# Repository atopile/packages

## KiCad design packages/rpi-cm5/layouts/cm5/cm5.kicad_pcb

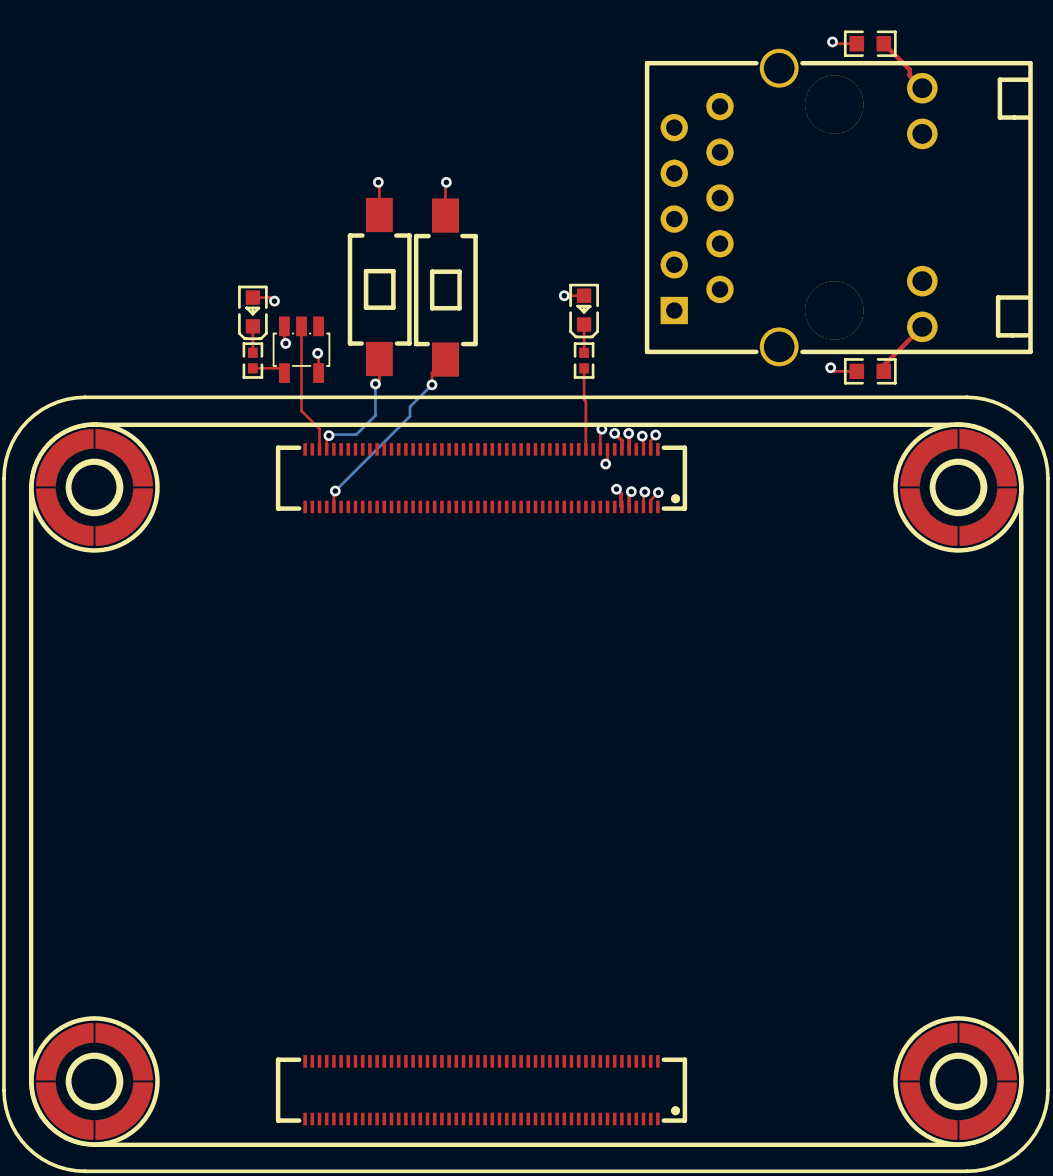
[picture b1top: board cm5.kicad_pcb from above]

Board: 4 copper layers, 17 parts (0 on the bottom side), 23 nets.

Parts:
CN1, CN2: CONN-SMD_DF40C-100DS-0.4V-51
D1: LED0603-RD-YELLOW
D2: LED0603-RD
R1, R2: 2kΩ ±1% 62.5mW; R0402
R3, R4: 470Ω ±1% 100mW; R0603
RJ1: RJ45-TH_HR911130A
SW1, SW2: SW-SMD_L6.0-W3.3-LS8.0
U1: SOT-23-5_L3.0-W1.7-P0.95-LS2.8-BR
U2, U3, U4, U5: SMD_BD5.6-D4.1
U6: cm5

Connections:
-pins[2]-0: CN1.99, RJ1.P8
-pins[3]: CN1.2, RJ1.P4
-pins[4]-0: CN1.98, RJ1.P9
-pins[5]: CN1.3, RJ1.P7
-pins[8]: CN1.96, RJ1.P6
-pins[9]: CN1.5, RJ1.P3
-pins[10]: CN1.95, RJ1.P5
-pins[11]: CN1.6, RJ1.P2
-pins[14]: CN1.93, RJ1.12
-pins[16]: CN1.92, RJ1.13
-pins[76]: CN1.57, CN1.58, CN1.59, CN1.60, CN1.61, CN1.62
-pins[92]: CN1.54, SW1.1
Y: R2.2, U1.4
cm5-cathode-0: D1.1, R1.1
cm5-cathode-1: D2.1, R2.1
cm5-pins[20]: CN1.90, R1.2
cm5-pins[87]-0: CN1.44, CN1.45
cm5-pins[94]: CN1.53, U1.2
gnd: CN1.1, CN1.4, CN1.7, CN1.11, CN1.16, CN1.21, CN1.26, CN1.30, CN1.33, CN1.37, CN1.49, CN1.65, CN1.68, CN1.71, CN1.74, CN1.79, CN1.84, CN1.89, CN1.94, CN1.97, CN1.100, CN2.4, CN2.7, CN2.10, CN2.13, CN2.16, CN2.19, CN2.22, CN2.28, CN2.31, CN2.34, CN2.37, CN2.40, CN2.43, CN2.46, CN2.49, CN2.52, CN2.55, CN2.58, CN2.61, CN2.64, CN2.67, CN2.70, CN2.73, CN2.82, CN2.85, CN2.88, CN2.91, CN2.94, CN2.97, RJ1.SHIELD0, RJ1.SHIELD1, SW1.2, SW2.2, U1.3, U2.1, U2.2, U2.3, U2.4, U3.1, U3.2, U3.3, U3.4, U4.1, U4.2, U4.3, U4.4, U5.1, U5.2, U5.3, U5.4
hv: CN1.39, CN1.42, CN1.43, D1.2, D2.2, R3.1, R4.1, U1.5
pins[91]: CN1.46, SW2.1
rj45-anode-0: R3.2, RJ1.11
rj45-anode-1: R4.2, RJ1.14

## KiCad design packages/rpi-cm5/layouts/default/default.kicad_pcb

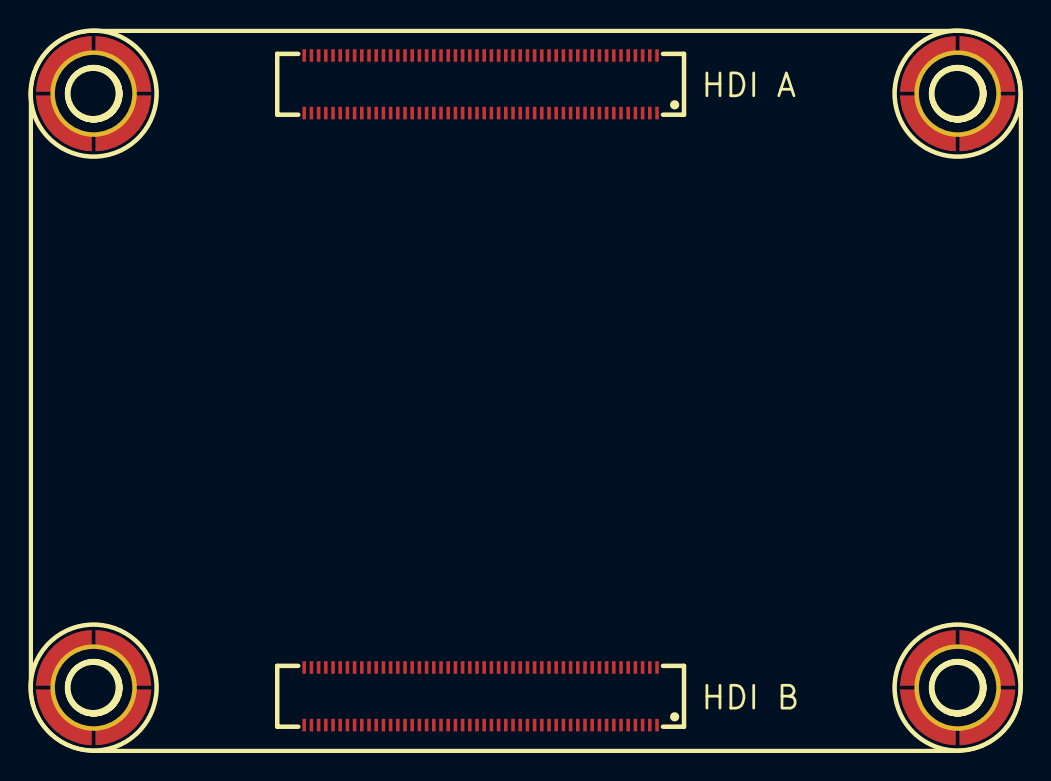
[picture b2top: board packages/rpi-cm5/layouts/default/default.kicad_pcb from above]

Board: 4 copper layers, 7 parts (0 on the bottom side), 5 nets, no tracks yet.

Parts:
CN1, CN2: CONN-SMD_DF40C-100DS-0.4V-51
U1, U2, U3, U4: SMD_BD5.6-D4.1
U5: cm5

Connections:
lv: CN1.1, CN1.4, CN1.7, CN1.11, CN1.16, CN1.21, CN1.26, CN1.30, CN1.33, CN1.37, CN1.49, CN1.65, CN1.68, CN1.71, CN1.74, CN1.79, CN1.84, CN1.89, CN1.94, CN1.97, CN1.100, CN2.4, CN2.7, CN2.10, CN2.13, CN2.16, CN2.22, CN2.28, CN2.31, CN2.34, CN2.37, CN2.40, CN2.43, CN2.46, CN2.49, CN2.52, CN2.55, CN2.58, CN2.61, CN2.64, CN2.67, CN2.70, CN2.73, CN2.82, CN2.85, CN2.88, CN2.91, CN2.94, CN2.97
power_1v8-hv: CN1.44, CN1.45
power_3v3-hv: CN1.42, CN1.43
power_3v3-lv: U1.1, U1.2, U1.3, U1.4, U1.5, U2.1, U2.2, U2.3, U2.4, U2.5, U3.1, U3.2, U3.3, U3.4, U3.5, U4.1, U4.2, U4.3, U4.4, U4.5
power_5v-hv: CN1.57, CN1.58, CN1.59, CN1.60, CN1.61, CN1.62

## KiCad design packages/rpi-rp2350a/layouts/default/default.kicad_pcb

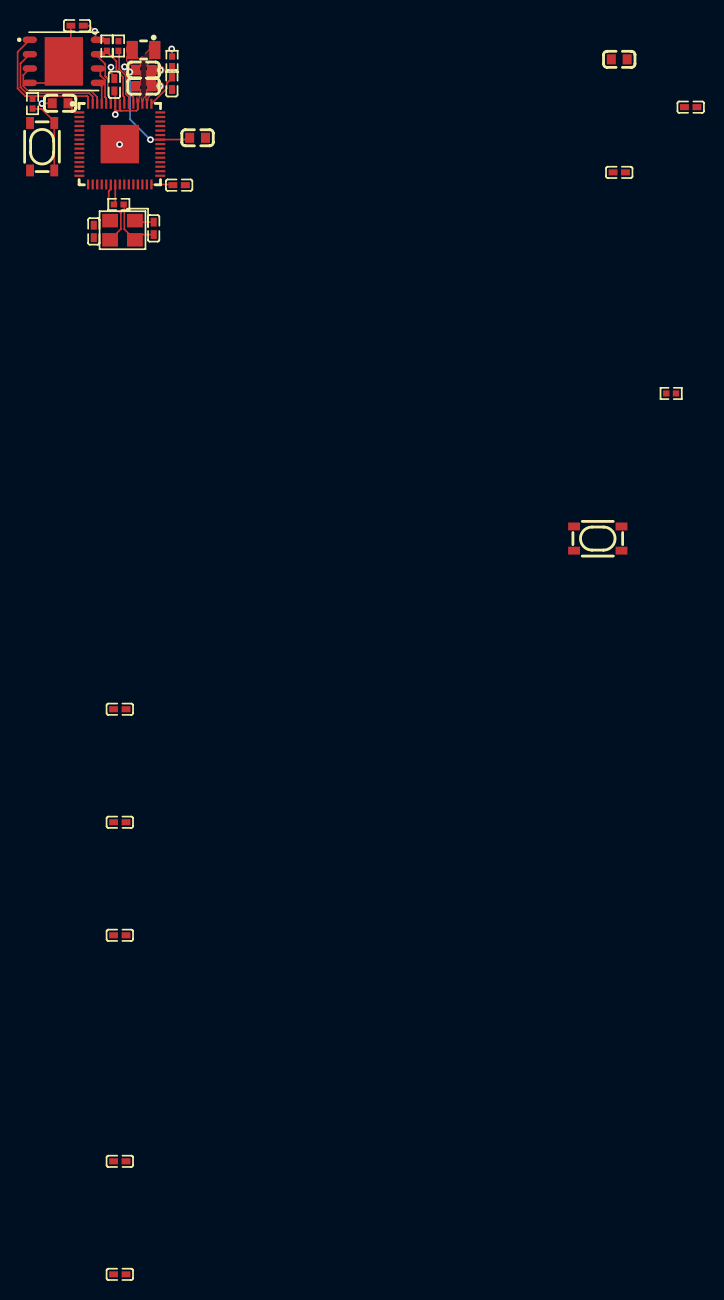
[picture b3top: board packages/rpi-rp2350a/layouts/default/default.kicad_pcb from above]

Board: 2 copper layers, 30 parts (0 on the bottom side), 20 nets.

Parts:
C1, C2, C5, C6, C7, C8, C9, C10, C11, C15, C16, C17, C18: 100nF ±10% 16V X7R; C0402-b3ef17
C3, C4, C12, C13, C14: 4.7µF ±10% 10V X5R; C0603-bd72f6
L1: IND-SMD_L2.0-W1.6_AOTA-B201610S3R3-101-T-1c9b19
R1, R2: 27Ω ±1% 62.5mW; R0402-56259e
R3, R6: 10kΩ ±1% 62.5mW; R0402-56259e
R4: 1kΩ ±1% 62.5mW; R0402-56259e
R5: 33Ω ±1% 62.5mW; R0402-56259e
U1: QFN-60_L7.0-W7.0-P0.40-TL-EP3.4-c01870
U2: WSON-8_L6.0-W5.0-P1.27-BL-EP-5c84f1
U3, U4: KEY-SMD_4P-L4.2-W3.2-P2.20-LS4.6-a2ccf0
XTAL1: CRYSTAL-SMD_4P-L3.2-W2.5-BL-e199c8

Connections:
QSPI_SCLK: U1.56, U2.6
QSPI_SD0: U1.57, U2.5
QSPI_SD1: U1.59, U2.2
QSPI_SD2: U1.58, U2.3
QSPI_SD3: U1.55, U2.7
QSPI_SS: R3.1, U1.60, U2.1
RUN: R6.1, U1.26
USB_DM: R1.2, U1.51
USB_DP: R2.2, U1.52
VREG_AVDD: C18.1, R5.2, U1.46
VREG_FB: C1.1, C2.1, C3.1, C4.1, L1.1, U1.6, U1.23, U1.39, U1.50
VREG_LX: L1.2, U1.48
XIN: C17.1, U1.21, XTAL1.3
XOUT: R4.2, U1.22
crystal_oscillator-net: C16.1, R4.1, XTAL1.4
gnd: U3.3, U3.4
gnd-1: C1.2, C2.2, C3.2, C4.2, C5.2, C6.2, C7.2, C8.2, C9.2, C10.2, C11.2, C12.2, C13.2, C14.2, C15.2, C16.2, C17.2, C18.2, U1.47, U1.61, U2.4, U2.9, U4.3, U4.4, XTAL1.1
hv: C5.1, C6.1, C7.1, C8.1, C9.1, C10.1, C11.1, C12.1, C13.1, C14.1, C15.1, R5.1, U1.1, U1.11, U1.20, U1.30, U1.38, U1.45, U1.49, U1.53, U1.54, U2.8
net: R6.2, U4.1, U4.2
net-1: R3.2, U3.1, U3.2

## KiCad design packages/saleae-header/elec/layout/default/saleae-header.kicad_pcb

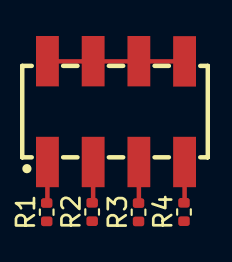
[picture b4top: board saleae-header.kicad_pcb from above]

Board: 2 copper layers, 5 parts (0 on the bottom side), 5 nets.

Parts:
R1, R2, R3, R4: Chip Resistor - Surface Mount 1KOhms ±5% 1/16W 04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; R0402
U1: HDR-SMD_8P-P2.54-V-M-R2-C4-LS7.4

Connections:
_1: R1.2, U1.1
_3: R2.2, U1.3
_5: R3.2, U1.5
_7: R4.2, U1.7
gnd: U1.2, U1.4, U1.6, U1.8

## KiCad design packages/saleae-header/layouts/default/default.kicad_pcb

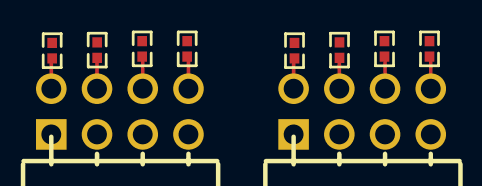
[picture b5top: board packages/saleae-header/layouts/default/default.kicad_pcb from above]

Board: 2 copper layers, 10 parts (0 on the bottom side), 10 nets.

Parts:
R1, R2, R3, R4, R5, R6, R7, R8: 1000Ω; R0402
U1, U2: HDR-TH_8P-P2.54-H-F-R2-C4-W8.5

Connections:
2: R1.2, U1.2
4: R2.2, U1.4
6: R3.2, U1.6
8: R4.2, U1.8
headers[1]-2: R5.2, U2.2
headers[1]-4: R6.2, U2.4
headers[1]-6: R7.2, U2.6
headers[1]-8: R8.2, U2.8
headers[1]-reference-lv: U2.1, U2.3, U2.5, U2.7
lv: U1.1, U1.3, U1.5, U1.7
